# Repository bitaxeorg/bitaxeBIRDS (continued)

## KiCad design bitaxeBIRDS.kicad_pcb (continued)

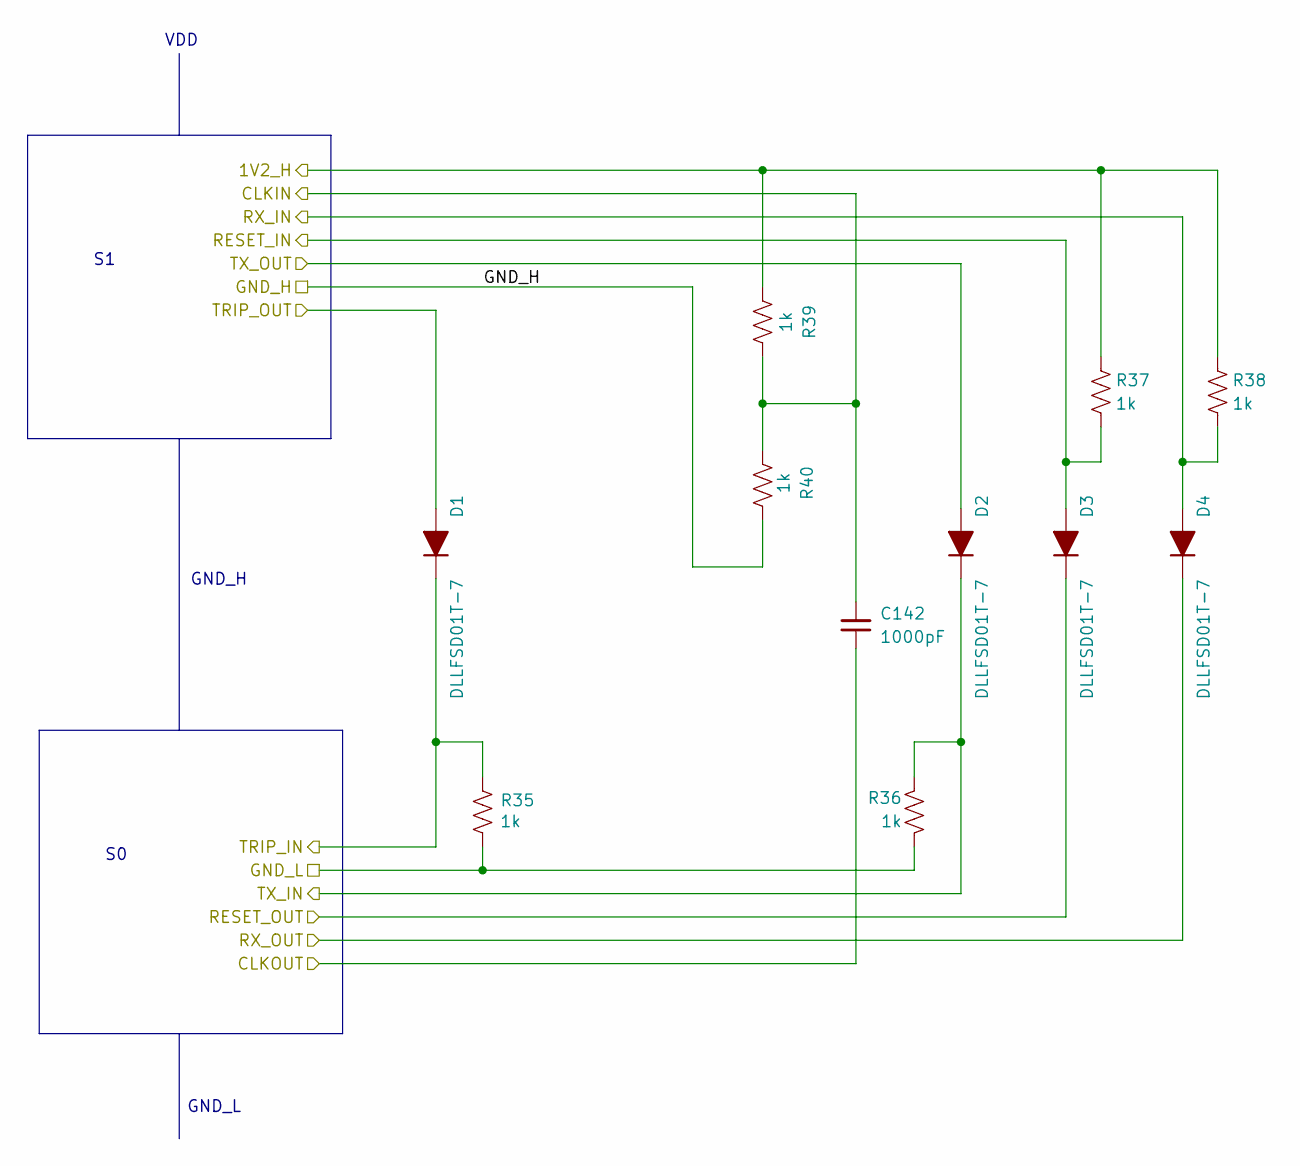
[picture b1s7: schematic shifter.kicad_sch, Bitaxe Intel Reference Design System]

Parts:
C142: 1000pF; C_0402_1005Metric; PARTNO GRM155R71H102KA01D
D1, D2, D3, D4: DLLFSD01T-7; D_SOD-523; PARTNO DLLFSD01T-7
R35, R36, R37, R38, R39, R40: 1k; R_0402_1005Metric; PARTNO RC0402FR-071KL

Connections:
/ASIC/1V2-2: R37.2, R38.1, R39.1; also elsewhere on the board
/ASIC/GND2: R40.2; also elsewhere on the board
/ASIC/REFCLKIN2: C142.2, R39.2, R40.1; also elsewhere on the board
/ASIC/REFCLKOUT1: C142.1; also elsewhere on the board
/ASIC/shifter1-2/RESET_IN: D3.A, R37.1; also elsewhere on the board
/ASIC/shifter1-2/RESET_OUT: D3.K; also elsewhere on the board
/ASIC/shifter1-2/RX_IN: D4.A, R38.2; also elsewhere on the board
/ASIC/shifter1-2/RX_OUT: D4.K; also elsewhere on the board
/ASIC/shifter1-2/TRIP_IN: D1.K, R35.1; also elsewhere on the board
/ASIC/shifter1-2/TRIP_OUT: D1.A; also elsewhere on the board
/ASIC/shifter1-2/TX_IN: D2.K, R36.1; also elsewhere on the board
/ASIC/shifter1-2/TX_OUT: D2.A; also elsewhere on the board
GND: R35.2, R36.2; also elsewhere on the board

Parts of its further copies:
C143, C144: 1000pF; C_0402_1005Metric; PARTNO GRM155R71H102KA01D
D5, D6, D7, D8, D9, D10, D11, D12: DLLFSD01T-7; D_SOD-523; PARTNO DLLFSD01T-7
R41, R42, R43, R44, R45, R46, R47, R48, R49, R50, R51, R52: 1k; R_0402_1005Metric; PARTNO RC0402FR-071KL

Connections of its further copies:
/ASIC/1V2-3: R43.2, R44.1, R45.1; also elsewhere on the board
/ASIC/1V2-4: R49.2, R50.1, R51.1; also elsewhere on the board
/ASIC/GND2: R41.2, R42.2; also elsewhere on the board
/ASIC/GND3: R46.2, R47.2, R48.2; also elsewhere on the board
/ASIC/GND4: R52.2; also elsewhere on the board
/ASIC/REFCLKIN3: C143.2, R45.2, R46.1; also elsewhere on the board
/ASIC/REFCLKIN4: C144.2, R51.2, R52.1; also elsewhere on the board
/ASIC/REFCLKOUT2: C143.1; also elsewhere on the board
/ASIC/REFCLKOUT3: C144.1; also elsewhere on the board
/ASIC/shifter2-3/RESET_IN: D7.A, R43.1; also elsewhere on the board
/ASIC/shifter2-3/RESET_OUT: D7.K; also elsewhere on the board
/ASIC/shifter2-3/RX_IN: D8.A, R44.2; also elsewhere on the board
/ASIC/shifter2-3/RX_OUT: D8.K; also elsewhere on the board
/ASIC/shifter2-3/TRIP_IN: D5.K, R41.1; also elsewhere on the board
/ASIC/shifter2-3/TRIP_OUT: D5.A; also elsewhere on the board
/ASIC/shifter2-3/TX_IN: D6.K, R42.1; also elsewhere on the board
/ASIC/shifter2-3/TX_OUT: D6.A; also elsewhere on the board
/ASIC/shifter3-4/RESET_IN: D11.A, R49.1; also elsewhere on the board
/ASIC/shifter3-4/RESET_OUT: D11.K; also elsewhere on the board
/ASIC/shifter3-4/RX_IN: D12.A, R50.2; also elsewhere on the board
/ASIC/shifter3-4/RX_OUT: D12.K; also elsewhere on the board
/ASIC/shifter3-4/TRIP_IN: D9.K, R47.1; also elsewhere on the board
/ASIC/shifter3-4/TRIP_OUT: D9.A; also elsewhere on the board
/ASIC/shifter3-4/TX_IN: D10.K, R48.1; also elsewhere on the board
/ASIC/shifter3-4/TX_OUT: D10.A; also elsewhere on the board

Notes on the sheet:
GND_H
VDD
GND_L

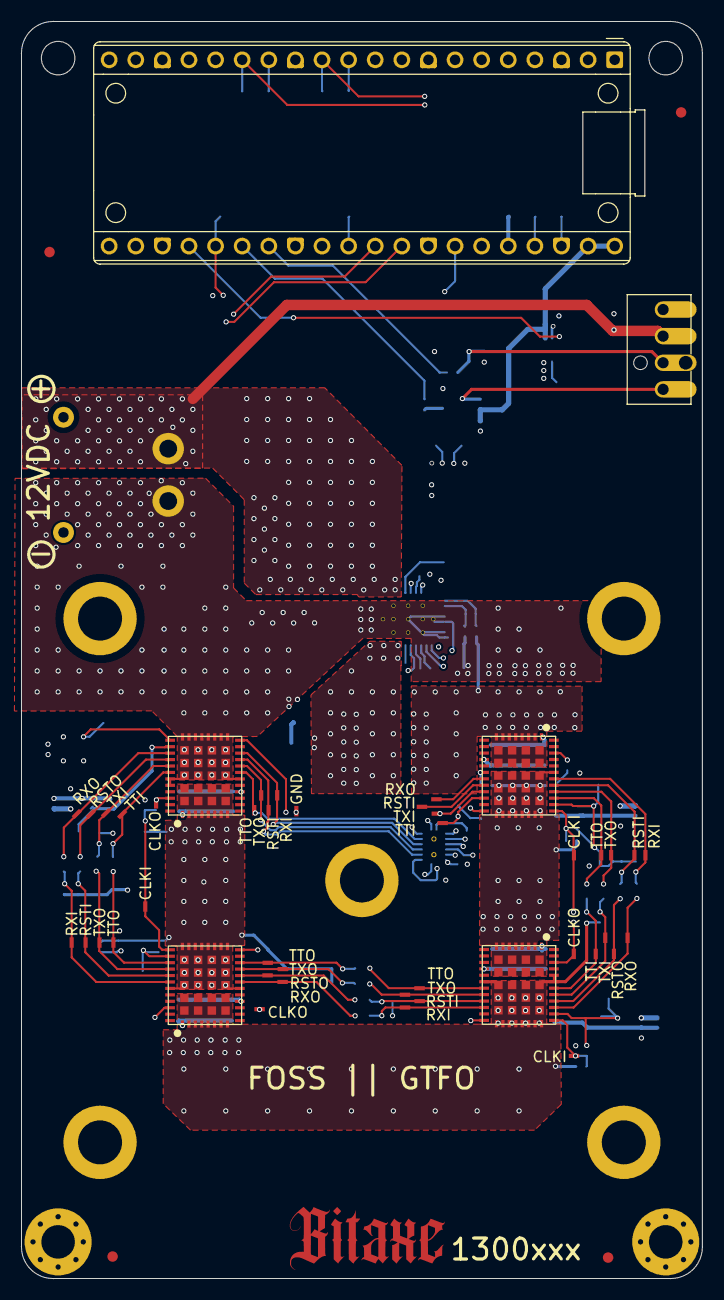
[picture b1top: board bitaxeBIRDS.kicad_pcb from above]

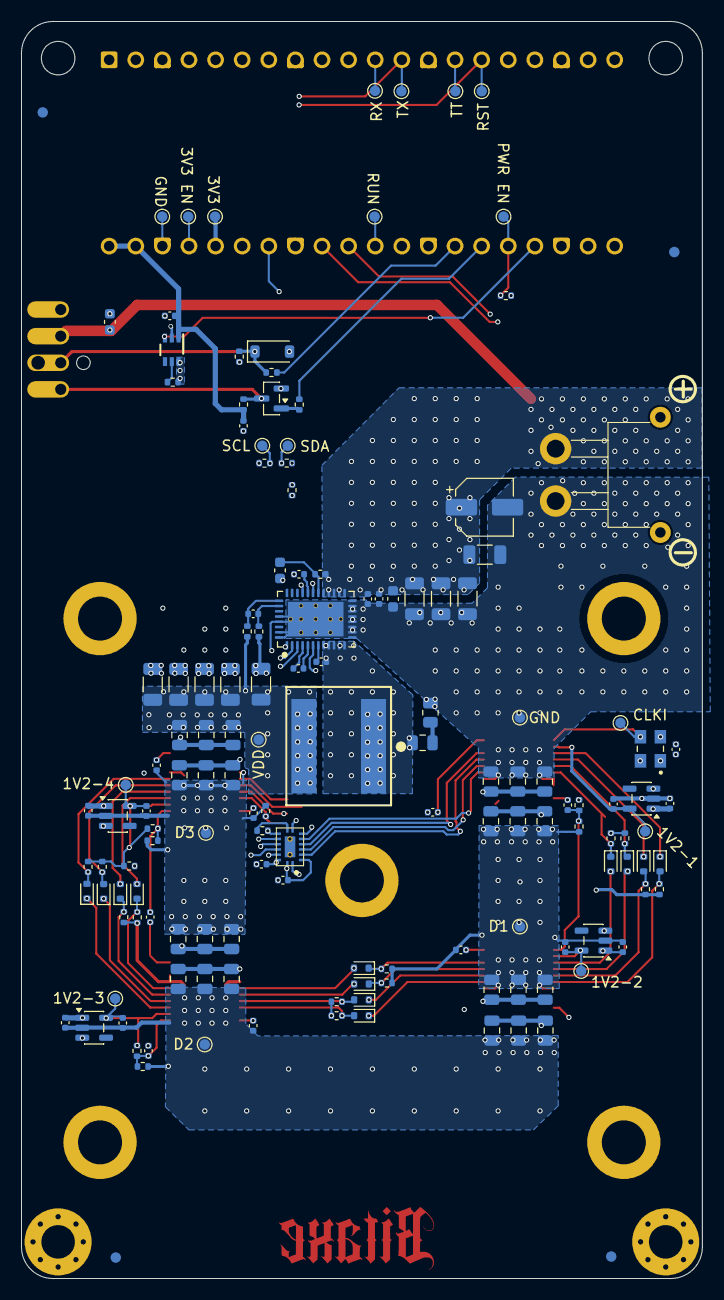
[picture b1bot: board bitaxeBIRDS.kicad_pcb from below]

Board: 6 copper layers, 65.0 x 120.0 mm, 199 parts (147 on the bottom side), 94 nets.

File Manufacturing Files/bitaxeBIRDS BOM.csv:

"Qty","Reference","Value","PARTNO","Footprint","DK","LCSC"
"2","A1,A3","BZM2_MODE0","","bitaxe:bzm2","",""
"2","A2,A4","BZM2_MODE1","","bitaxe:bzm2","",""
"1","C2","27uF","APXG250ARA270MF46G","Capacitor_SMD:CP_Elec_5x5.9","565-APXG250ARA270MF46GCT-ND",""
"1","C11","4.7uF","GRM155R61A475MEAAD","Capacitor_SMD:C_0402_1005Metric","490-14306-1-ND",""
"1","C13","4.7nF","GRM155R71E472KA01D","Capacitor_SMD:C_0402_1005Metric","490-1309-1-ND",""
"1","C14","2.2nF","490-8257-1-ND","Capacitor_SMD:C_0402_1005Metric","490-8257-1-ND",""
"1","C17","1000pF","CC0805KRX7R9BB102","Capacitor_SMD:C_0805_2012Metric","311-1127-1-ND",""
"1","C18","100pF","CC0402JRNPO9BN101","Capacitor_SMD:C_0402_1005Metric","311-1024-1-ND",""
"1","C20","47uF","GRM31CR61A476ME15L","Capacitor_SMD:C_1206_3216Metric","490-5528-1-ND",""
"1","C76","10uF","GRM188R61E106KA73D","Capacitor_SMD:C_0603_1608Metric","490-18214-1-ND",""
"3","C142,C143,C144","1000pF","GRM155R71H102KA01D","Capacitor_SMD:C_0402_1005Metric","490-1303-1-ND",""
"5","C16,C57,C58,C59,C77","0.1uF","KGM05AR71C104KH","Capacitor_SMD:C_0402_1005Metric","478-KGM05AR71C104KHCT-ND",""
"4","C21,C22,C23,C24","100uF","CL31A107MQHNNNE","Capacitor_SMD:C_1206_3216Metric","1276-1782-1-ND",""
"4","C3,C4,C5,C6","22uF","TMK316BBJ226ML-T","Capacitor_SMD:C_1206_3216Metric","587-3246-1-ND",""
"5","C60,C61,C62,C63,C64","120pF","0402X104K100CT","Capacitor_SMD:C_0402_1005Metric","1292-1639-1-ND",""
"9","C7,C19,C25,C26,C27,C28,C45,C68,C72","1uF","EMK105BJ105MV-F","Capacitor_SMD:C_0402_1005Metric","587-5514-1-ND",""
"24","C83,C84,C85,C91,C92,C93,C99,C100,C101,C107,C108,C109,C115,C116,C117,C123,C124,C125,C131,C132,C133,C139,C140,C141","100uF","GRM21BR60G107ME11K","Capacitor_SMD:C_0805_2012Metric","490-GRM21BR60G107ME11KCT-ND",""
"3","C9,C10,C15","1uF","TMK107B7105KA-T","Capacitor_SMD:C_0402_1005Metric","587-2984-1-ND",""
"1","D13","3.3V Zener","DDZ9684-7","Diode_SMD:D_SOD-123","DDZ9684-7DICT-ND",""
"12","D1,D2,D3,D4,D5,D6,D7,D8,D9,D10,D11,D12","DLLFSD01LPH4-7B","DLLFSD01LPH4-7B","bitaxe:DIODE_DLLFSD01LPH4-7B_DIO","31-DLLFSD01LPH4-7BCT-ND",""
"1","J1","XT30","XT30PW-M","bitaxe:XT30PW-M","~","C431092"
"1","J4","Conn_01x04","0470531000","bitaxe:470531000","WM4330-ND",""
"1","L1","1.2uH","XAL1060-122MEC","bitaxe:XAL1060122MEC","2457-XAL1060-122MEC-ND",""
"1","Q1","BSS138","BSS138K-13","Package_TO_SOT_SMD:SOT-23","BSS138K-13DICT-ND",""
"1","R5","10","RC0402FR-0710RL","Resistor_SMD:R_0402_1005Metric","311-10.0LRCT-ND",""
"1","R6","1","ESR10EZPJ1R0","Resistor_SMD:R_0805_2012Metric","RHM1KTR-ND",""
"1","R26","20k","RC0402FR-0720KL","Resistor_SMD:R_0402_1005Metric","311-20.0KLRCT-ND",""
"1","R33","5.6k","RC0402FR-075K6L","Resistor_SMD:R_0402_1005Metric","311-5.6KLRCT-ND",""
"2","R1,R20","1k","RC0402FR-071KL","Resistor_SMD:R_0402_1005Metric","311-1.00KLRCT-ND",""
"3","R2,R3,R34","10k","RC0402JR-0710KL","Resistor_SMD:R_0402_1005Metric","311-10KJRCT-ND",""
"3","R23,R24,R25","4.7k","RC0402FR-074K7L","Resistor_SMD:R_0402_1005Metric","311-4.7KLRCT-ND",""
"18","R35,R36,R37,R38,R39,R40,R41,R42,R43,R44,R45,R46,R47,R48,R49,R50,R51,R52","1k","RC0402JR-071KL","Resistor_SMD:R_0402_1005Metric","311-1.0KJRCT-ND",""
"2","R7,R8","49.9","RC0402FR-0749R9L","Resistor_SMD:R_0402_1005Metric","311-49.9LRCT-ND",""
"1","U2","TPS546D24SRVFR","TPS546D24SRVFR","bitaxe:LQFN40-CLIP","296-TPS546D24SRVFRCT-ND",""
"1","U5","TPS22919DCKR","TPS22919DCKR","bitaxe:DCK0006A_N","296-TPS22919DCKRCT-ND",""
"1","U8","SN74AXC4T774","SN74AXC4T774BQBR","bitaxe:BQB0016A-MFG","296-SN74AXC4T774BQBRCT-ND",""
"1","U9","Raspberry Pi Pico","","bitaxe:RaspberryPi_Pico_Common_THT","",""
"4","U3,U12,U14,U15","TLV75512PDQNR","TLV75512PDQNR","bitaxe:DQN0004A","296-51785-1-ND",""
"1","Y2","50MHz","SX3M50.000E20F30THN","bitaxe:OSC_ECS-3225MV-500-CN-TR","",""

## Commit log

2025-10-02 created bitaxeBIRDS from bitaxeGT-800xxxx. moved over RP2040. initial import.
2025-10-02 started to piece in the BZM2 into schematic
2025-10-02 finished adding ASICs to schematic. Change VR to single phase 2.8V output
2025-10-03 switched to smaller level shifter diodes. switched ASIC modes
2025-10-03 switched to TINY LDOs.
2025-10-07 more routing
2025-10-28 Added RP Pico W2 to schematic. Fixed Domain 1-2 level shifter pins. Added test points
2025-10-28 switched to THT RPi Pico 2W style. Made 8mm taller.
2025-10-29 lots of routing
2025-10-29 routing done, needs DRC and cleanup
2025-10-30 Removed EMC2103, added discrete fan control, DRC pass, fixed logo.
2025-10-30 power plane cleanup. added field vias. generated BOM
2025-10-30 update TPS546D24 to `S` variant. Add render and readme.
2025-11-06 Correct U8 value field.
2025-11-06 unify 1k resistor part numbers
2025-11-06 update C9 and C10 to the correct 0603 footprint. Change C15 part number to be 0402
2025-11-06 update 50MHz osc part number.
2025-11-06 change Y2 OSC part number back.
2025-11-24 Add firmware support details and clarify Gerber policy
    Updated README to include preliminary support for bitaxe-raw-pico firmware and clarified Gerber availability.
2025-11-30 TX_IN modified to pull low to GND_L in level shifter (Closes: #2)
2025-11-30 Added footprint library configuration so KiCad can find bitaxe.pretty
    Also, we can ignore generated files for the BOM
2025-11-30 Rerouoted the traces for the pull-down resistor on TX_IN for each level
2026-02-09 add inductor footprint
2026-02-09 clean up some of the schematic errors for #4
2026-02-09 cleaned up lots of ERC errors and warnings for #4
2026-02-10 fix part numbers for C60-C64 for #5
2026-02-10 added pull resistors for #1
2026-02-10 changed all the level shifting diodes to SOD-523 packages for #6
2026-02-10 change IO voltage LDOs to bigger packages for #6
2026-02-15 fix pinsel connection on ASIC 3 for #7
